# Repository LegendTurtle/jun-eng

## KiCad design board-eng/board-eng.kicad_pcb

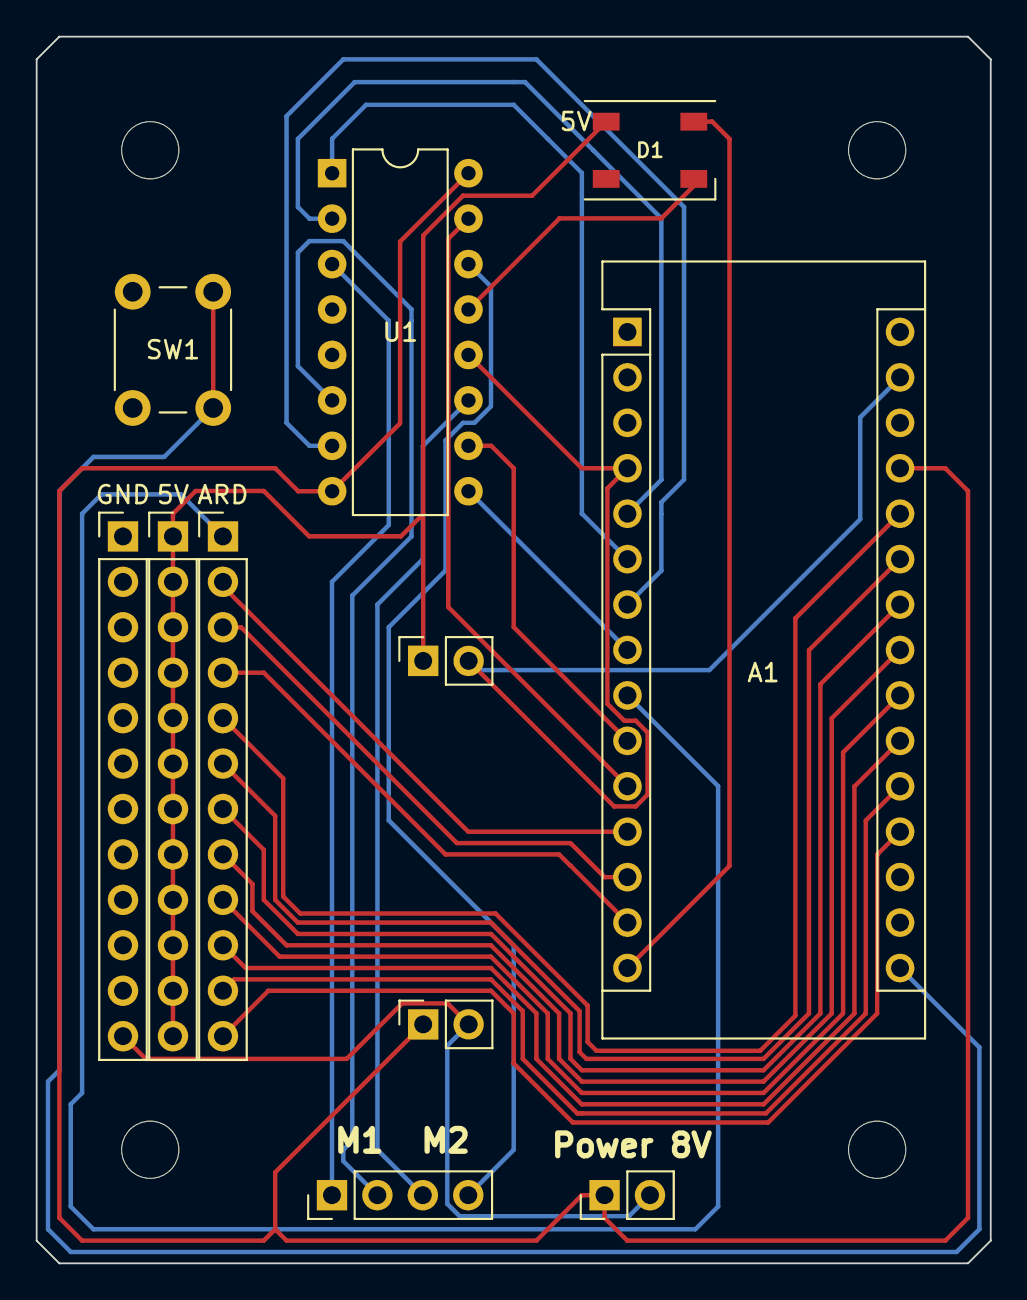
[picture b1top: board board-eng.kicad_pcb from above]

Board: 2 copper layers, 53.3 x 68.6 mm, 15 parts (0 on the bottom side), 27 nets.

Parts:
5V: Conn_01x12_Male; PinHeader_1x12_P2.54mm_Vertical
A1: Arduino_Nano_Every; Arduino_Nano
ARD: Conn_01x12_Male; PinHeader_1x12_P2.54mm_Vertical
D1: WS2812B; LED_WS2812B_PLCC4_5.0x5.0mm_P3.2mm
GND: Conn_01x12_Male; PinHeader_1x12_P2.54mm_Vertical
H1, H2, H3, H4: MountingHole; MountingHole_3.2mm_M3
J1: Conn_01x04_Male; PinHeader_1x04_P2.54mm_Vertical
J6: Conn_01x02_Female; PinSocket_1x02_P2.54mm_Vertical
J7: Conn_01x02_Male; PinHeader_1x02_P2.54mm_Vertical
Power 5V: Conn_01x02_Female; PinSocket_1x02_P2.54mm_Vertical
SW1: SW_DIP_x01; SW_PUSH_6mm
U1: L293D; DIP-16_W7.62mm

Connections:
5V: 5V.1, 5V.2, 5V.3, 5V.4, 5V.5, 5V.6, 5V.7, 5V.8, 5V.9, 5V.10, 5V.11, 5V.12, D1.1 (VDD), Power 5V.1
8V: A1.27 (+5V), J6.1, J7.1, U1.8 (VCC2), U1.16 (VCC1)
A0: A1.19 (A0), ARD.12
A1: A1.20 (A1), ARD.11
A2: A1.21 (A2), ARD.10
A3: A1.22 (A3), ARD.9
A4: A1.23 (SDA/A4), ARD.8
A5: A1.24 (SCL/A5), ARD.7
A6: A1.25 (A6), ARD.6
A7: A1.26 (A7), ARD.5
BTN: A1.16 (SCK), SW1.1
D6: A1.9 (D6), ARD.1
D9: A1.12 (D9), ARD.2
D10: A1.13 (D10), ARD.3
D11: A1.14 (MOSI), ARD.4
EN1: A1.6 (D3), U1.1 (EN1,2)
EN2: A1.8 (D5), U1.9 (EN3,4)
GND: A1.4 (GND), A1.29 (GND), D1.3 (VSS), GND.1, GND.2, GND.3, GND.4, GND.5, GND.6, GND.7, GND.8, GND.9, GND.10, GND.11, GND.12, J6.2, J7.2, Power 5V.2, SW1.2, U1.4 (GND), U1.5 (GND), U1.12 (GND), U1.13 (GND)
LED: A1.15 (MISO), D1.4 (DIN)
M1A-IN: A1.5 (D2), U1.2 (1A)
M1A-OUT: J1.1, U1.3 (1Y)
M1B-IN: A1.7 (D4), U1.7 (2A)
M1B-OUT: J1.2, U1.6 (2Y)
M2A-IN: A1.10 (D7), U1.10 (3A)
M2A-OUT: J1.3, U1.11 (3Y)
M2B-IN: A1.11 (D8), U1.15 (4A)
M2B-OUT: J1.4, U1.14 (4Y)

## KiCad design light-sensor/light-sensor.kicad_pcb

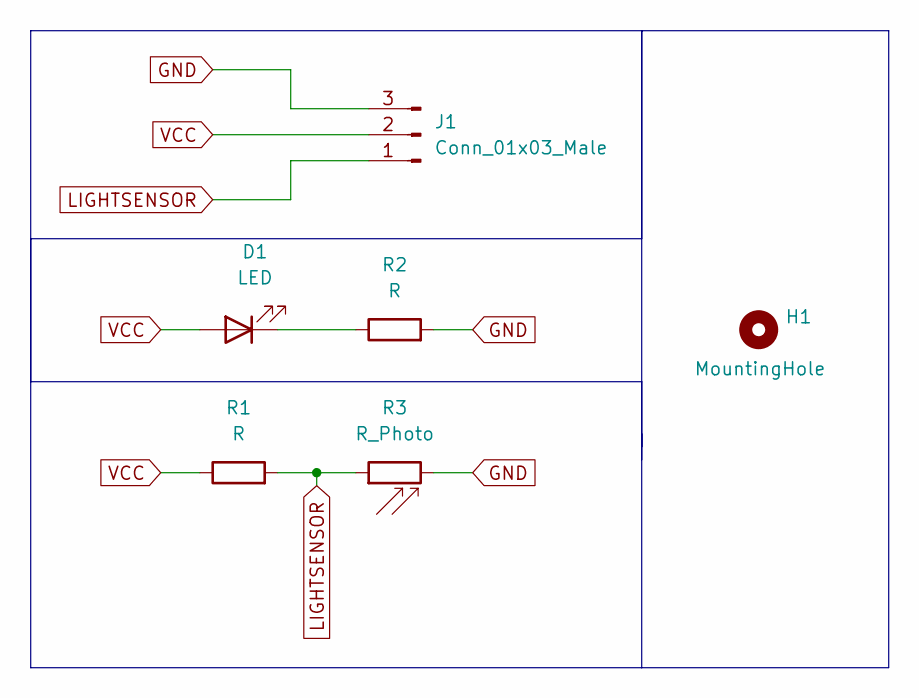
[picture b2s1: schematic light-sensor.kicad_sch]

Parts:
D1: LED; LED_D5.0mm
H1: MountingHole; MountingHole_3.2mm_M3
J1: Conn_01x03_Male; PinHeader_1x03_P2.54mm_Vertical
R1, R2: R; R_Axial_DIN0207_L6.3mm_D2.5mm_P7.62mm_Horizontal
R3: R_Photo; LED_D5.0mm

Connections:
GND: J1.3, R2.2, R3.2
LIGHTSENSOR: J1.1, R1.2, R3.1
unnamed: D1.1 (K), R2.1
VCC: D1.2 (A), J1.2, R1.1

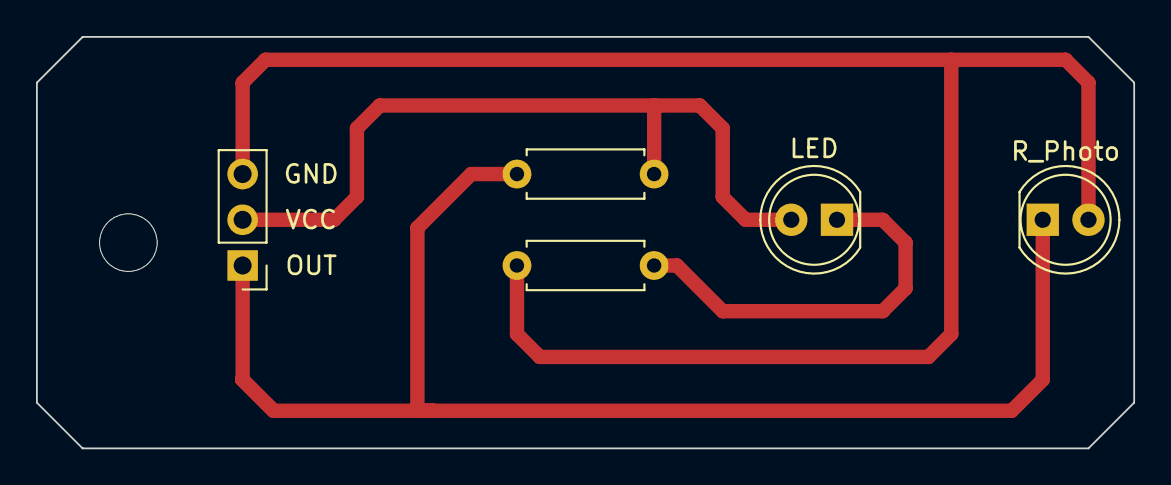
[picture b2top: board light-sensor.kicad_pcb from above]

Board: 2 copper layers, 61.0 x 22.9 mm, 6 parts (0 on the bottom side), 4 nets.

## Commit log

2025-05-12 main
2025-05-23 it works!
2025-05-24 beauty code
